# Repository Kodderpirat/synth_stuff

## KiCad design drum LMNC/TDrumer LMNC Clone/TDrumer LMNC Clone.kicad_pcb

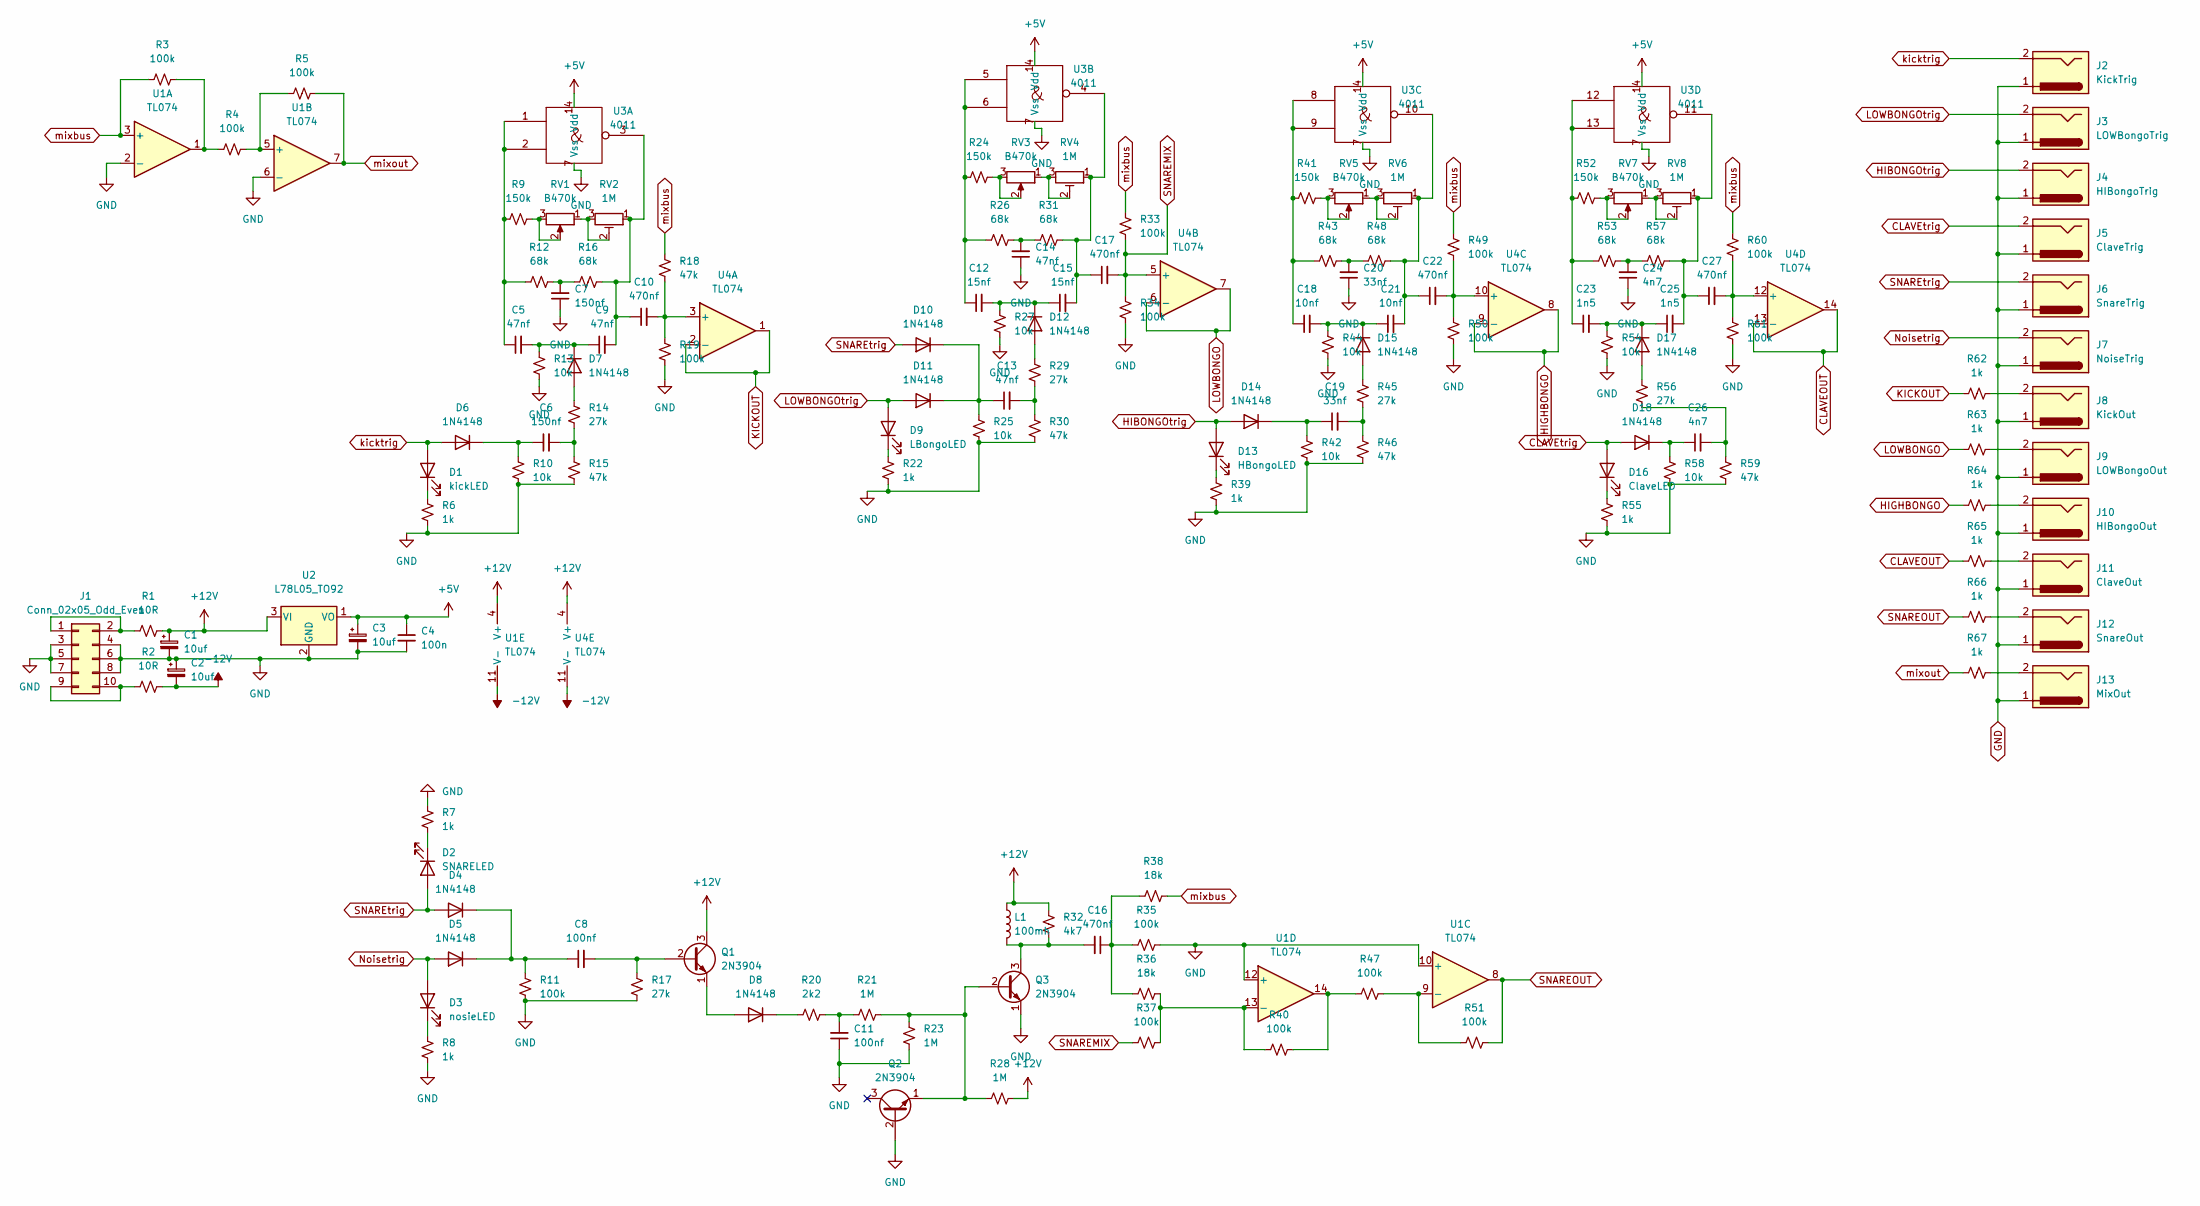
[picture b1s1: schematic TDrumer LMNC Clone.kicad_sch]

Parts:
C1, C2, C3: 10uf; CP_Radial_D5.0mm_P2.50mm
C4: 100n; C_Disc_D6.0mm_W2.5mm_P5.00mm
C5, C9, C13, C14: 47nf; C_Disc_D6.0mm_W2.5mm_P5.00mm
C6, C7: 150nf; C_Disc_D6.0mm_W2.5mm_P5.00mm
C8, C11: 100nf; C_Disc_D6.0mm_W2.5mm_P5.00mm
C10, C16, C17, C22, C27: 470nf; C_Disc_D6.0mm_W2.5mm_P5.00mm
C12, C15: 15nf; C_Disc_D6.0mm_W2.5mm_P5.00mm
C18, C21: 10nf; C_Disc_D6.0mm_W2.5mm_P5.00mm
C19, C20: 33nf; C_Disc_D6.0mm_W2.5mm_P5.00mm
C23, C25: 1n5; C_Disc_D6.0mm_W2.5mm_P5.00mm
C24, C26: 4n7; C_Disc_D6.0mm_W2.5mm_P5.00mm
D1: kickLED; PinSocket_1x02_P2.54mm_Vertical
D2: SNARELED; PinSocket_1x02_P2.54mm_Vertical
D3: nosieLED; PinSocket_1x02_P2.54mm_Vertical
D4, D5, D6, D7, D8, D10, D11, D12, D14, D15, D17, D18: 1N4148; D_DO-35_SOD27_P7.62mm_Horizontal
D9: LBongoLED; PinSocket_1x02_P2.54mm_Vertical
D13: HBongoLED; PinSocket_1x02_P2.54mm_Vertical
D16: ClaveLED; PinSocket_1x02_P2.54mm_Vertical
J1: Conn_02x05_Odd_Even; PinSocket_2x05_P2.54mm_Vertical
J2: KickTrig; PinSocket_1x02_P2.54mm_Vertical
J3: LOWBongoTrig; PinSocket_1x02_P2.54mm_Vertical
J4: HIBongoTrig; PinSocket_1x02_P2.54mm_Vertical
J5: ClaveTrig; PinSocket_1x02_P2.54mm_Vertical
J6: SnareTrig; PinSocket_1x02_P2.54mm_Vertical
J7: NoiseTrig; PinSocket_1x02_P2.54mm_Vertical
J8: KickOut; PinSocket_1x02_P2.54mm_Vertical
J9: LOWBongoOut; PinSocket_1x02_P2.54mm_Vertical
J10: HIBongoOut; PinSocket_1x02_P2.54mm_Vertical
J11: ClaveOut; PinSocket_1x02_P2.54mm_Vertical
J12: SnareOut; PinSocket_1x02_P2.54mm_Vertical
J13: MixOut; PinSocket_1x02_P2.54mm_Vertical
L1: 100mh; L_Axial_L17.5mm_D12.0mm_P20.32mm_Horizontal_Vishay_IM-10-46
Q1, Q2, Q3: 2N3904; TO-92_Inline
R1, R2: 10R; R_Axial_DIN0204_L3.6mm_D1.6mm_P7.62mm_Horizontal
R3, R4, R5, R11, R19, R33, R34, R35, R37, R40, R47, R49, R50, R51, R60, R61: 100k; R_Axial_DIN0204_L3.6mm_D1.6mm_P7.62mm_Horizontal
R6, R7, R8, R22, R39, R55, R62, R63, R64, R65, R66, R67: 1k; R_Axial_DIN0204_L3.6mm_D1.6mm_P7.62mm_Horizontal
R9, R24, R41, R52: 150k; R_Axial_DIN0204_L3.6mm_D1.6mm_P7.62mm_Horizontal
R10, R13, R25, R27, R42, R44, R54, R58: 10k; R_Axial_DIN0204_L3.6mm_D1.6mm_P7.62mm_Horizontal
R12, R16, R26, R31, R43, R48, R53, R57: 68k; R_Axial_DIN0204_L3.6mm_D1.6mm_P7.62mm_Horizontal
R14, R17, R29, R45, R56: 27k; R_Axial_DIN0204_L3.6mm_D1.6mm_P7.62mm_Horizontal
R15, R18, R30, R46, R59: 47k; R_Axial_DIN0204_L3.6mm_D1.6mm_P7.62mm_Horizontal
R20: 2k2; R_Axial_DIN0204_L3.6mm_D1.6mm_P7.62mm_Horizontal
R21, R23, R28: 1M; R_Axial_DIN0204_L3.6mm_D1.6mm_P7.62mm_Horizontal
R32: 4k7; R_Axial_DIN0204_L3.6mm_D1.6mm_P7.62mm_Horizontal
R36, R38: 18k; R_Axial_DIN0204_L3.6mm_D1.6mm_P7.62mm_Horizontal
RV1, RV3, RV5, RV7: B470k; PinSocket_1x03_P2.54mm_Vertical
RV2, RV4, RV6, RV8: 1M; PinSocket_1x03_P2.54mm_Vertical
U1, U4: TL074; DIP-14_W7.62mm
U2: L78L05_TO92; TO-92_Inline
U3: 4011; DIP-14_W7.62mm

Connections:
+5V: C3.1, C4.1, U2.1 (VO), U3.14 (Vdd)
+12V: C1.1, L1.1, Q1.3 (C), R1.2, R28.1, R32.2, U1.4 (V+), U2.3 (VI), U4.4 (V+)
-12V: C2.2, R2.2, U1.11 (V-), U4.11 (V-)
CLAVEOUT: R65.1, U4.13 (-), U4.14
CLAVEtrig: D16.2 (A), D18.2 (A), J5.2
GND: C1.2, C2.1, C3.2, C4.2, C7.1, C11.1, C14.1, C20.1, C24.1, J1.3, J1.4, J1.5, J1.6, J1.7, J1.8, J2.1, J3.1, J4.1, J5.1, J6.1, J7.1, J8.1, J9.1, J10.1, J11.1, J12.1, J13.1, Q2.2 (B), Q3.1 (E), R6.2, R7.1, R8.2, R10.2, R11.2, R13.2, R15.2, R17.2, R19.2, R22.2, R23.1, R25.2, R27.2, R30.2, R34.2, R35.2, R39.2, R42.2, R44.2, R46.2, R50.2, R54.2, R55.2, R58.2, R59.2, R61.2, U1.2 (-), U1.6 (-), U1.10 (+), U1.12 (+), U2.2 (GND), U3.7 (Vss)
HIBONGOtrig: D13.2 (A), D14.2 (A), J4.2
HIGHBONGO: R64.1, U4.8, U4.9 (-)
KICKOUT: R62.1, U4.1, U4.2 (-)
LOWBONGO: R63.1, U4.6 (-), U4.7
LOWBONGOtrig: D9.2 (A), D11.2 (A), J3.2
unnamed: C5.1, R9.1, R12.1, U3.1, U3.2
unnamed: C5.2, C9.1, D7.1 (K), R13.1
unnamed: C6.1, D6.1 (K), R10.1
unnamed: C6.2, R14.2, R15.1
unnamed: C7.2, R12.2, R16.1
unnamed: C8.1, D4.1 (K), D5.1 (K), R11.1
unnamed: C8.2, Q1.2 (B), R17.1
unnamed: C9.2, C10.1, R16.2, RV2.1, U3.3
unnamed: C10.2, R18.2, R19.1, U4.3 (+)
unnamed: C11.2, R20.2, R21.1
unnamed: C12.1, R24.1, R26.1, U3.5, U3.6
unnamed: C12.2, C15.1, D12.1 (K), R27.1
unnamed: C13.1, D10.1 (K), D11.1 (K), R25.1
unnamed: C13.2, R29.2, R30.1
unnamed: C14.2, R26.2, R31.1
unnamed: C15.2, C17.1, R31.2, RV4.1, U3.4
unnamed: C16.1, R35.1, R36.1, R38.1
unnamed: C16.2, L1.2, Q3.3 (C), R32.1
unnamed: C18.1, R41.1, R43.1, U3.8, U3.9
unnamed: C18.2, C21.1, D15.1 (K), R44.1
unnamed: C19.1, D14.1 (K), R42.1
unnamed: C19.2, R45.2, R46.1
unnamed: C20.2, R43.2, R48.1
unnamed: C21.2, C22.1, R48.2, RV6.1, U3.10
unnamed: C22.2, R49.2, R50.1, U4.10 (+)
unnamed: C23.1, R52.1, R53.1, U3.12, U3.13
unnamed: C23.2, C25.1, D17.1 (K), R54.1
unnamed: C24.2, R53.2, R57.1
unnamed: C25.2, C27.1, R57.2, RV8.1, U3.11
unnamed: C26.1, D18.1 (K), R58.1
unnamed: C26.2, R56.2, R59.1
unnamed: C27.2, R60.2, R61.1, U4.12 (+)
unnamed: D1.1 (K), R6.1
unnamed: D2.1 (K), R7.2
unnamed: D3.1 (K), R8.1
unnamed: D7.2 (A), R14.1
unnamed: D8.1 (K), R20.1
unnamed: D8.2 (A), Q1.1 (E)
unnamed: D9.1 (K), R22.1
unnamed: D12.2 (A), R29.1
unnamed: D13.1 (K), R39.1
unnamed: D15.2 (A), R45.1
unnamed: D16.1 (K), R55.1
unnamed: D17.2 (A), R56.1
unnamed: J1.1, J1.2, R1.1
unnamed: J1.9, J1.10, R2.1
unnamed: J8.2, R62.2
unnamed: J9.2, R63.2
unnamed: J10.2, R64.2
unnamed: J11.2, R65.2
unnamed: J12.2, R66.2
unnamed: J13.2, R67.2
unnamed: Q2.1 (E), Q3.2 (B), R21.2, R23.2, R28.2
unnamed: R3.2, R4.1, U1.1
unnamed: R4.2, R5.1, U1.5 (+)
unnamed: R9.2, RV1.2, RV1.3
unnamed: R24.2, RV3.2, RV3.3
unnamed: R36.2, R37.2, R40.1, U1.13 (-)
unnamed: R40.2, R47.1, U1.14
unnamed: R41.2, RV5.2, RV5.3
unnamed: R47.2, R51.1, U1.9 (-)
unnamed: R52.2, RV7.2, RV7.3
unnamed: RV1.1, RV2.2, RV2.3
unnamed: RV3.1, RV4.2, RV4.3
unnamed: RV5.1, RV6.2, RV6.3
unnamed: RV7.1, RV8.2, RV8.3
Noisetrig: D3.2 (A), D5.2 (A), J7.2
SNAREMIX: C17.2, R33.2, R34.1, R37.1, U4.5 (+)
SNAREOUT: R51.2, R66.1, U1.8
SNAREtrig: D2.2 (A), D4.2 (A), D10.2 (A), J6.2
kicktrig: D1.2 (A), D6.2 (A), J2.2
mixbus: R3.1, R18.1, R33.1, R38.2, R49.1, R60.1, U1.3 (+)
mixout: R5.2, R67.1, U1.7

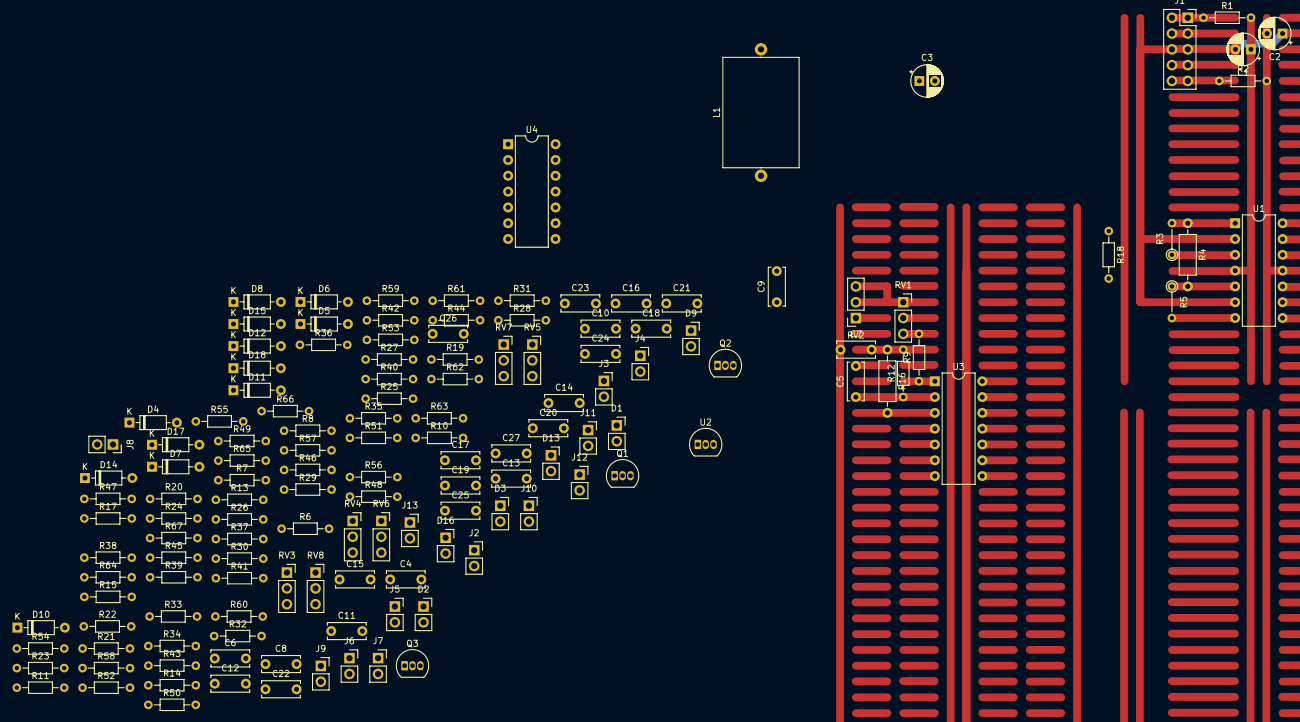
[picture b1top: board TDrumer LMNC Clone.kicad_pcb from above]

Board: 2 copper layers, 141 parts (0 on the bottom side), 84 nets.

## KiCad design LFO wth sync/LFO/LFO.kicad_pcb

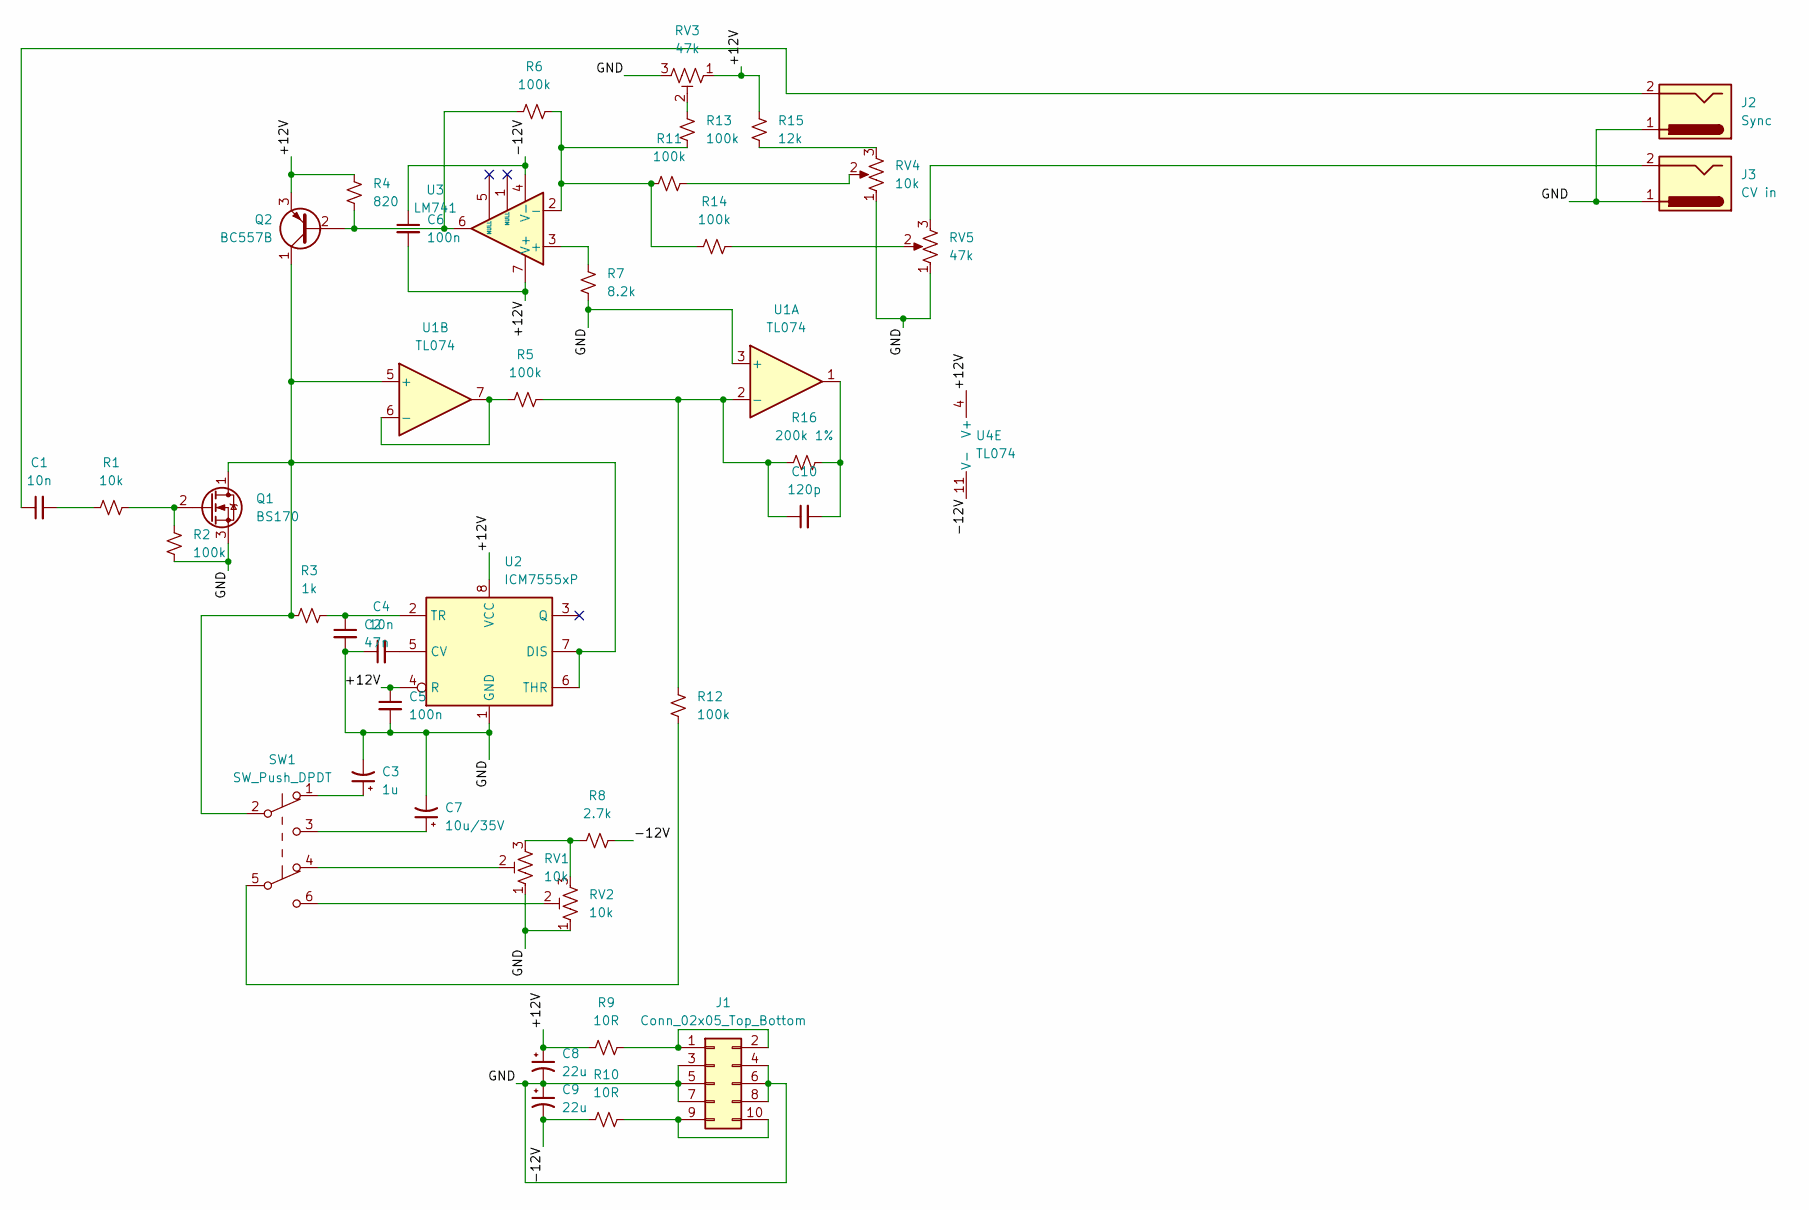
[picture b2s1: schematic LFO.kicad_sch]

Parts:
C1, C4: 10n; C_Disc_D10.5mm_W5.0mm_P5.00mm
C2: 47n; C_Disc_D10.5mm_W5.0mm_P5.00mm
C3: 1u; CP_Radial_D6.3mm_P2.50mm
C5, C6: 100n; C_Disc_D10.5mm_W5.0mm_P5.00mm
C7: 10u/35V; CP_Radial_D6.3mm_P2.50mm
C8, C9: 22u; CP_Radial_D6.3mm_P2.50mm
C10: 120p; C_Disc_D10.5mm_W5.0mm_P5.00mm
J1: Conn_02x05_Top_Bottom; PinHeader_2x05_P2.54mm_Vertical
J2: Sync; PinHeader_1x02_P2.54mm_Vertical
J3: CV in; PinHeader_1x02_P2.54mm_Vertical
Q1: BS170; TO-92_Inline
Q2: BC557B; TO-92_Inline
R1: 10k; R_Axial_DIN0207_L6.3mm_D2.5mm_P7.62mm_Horizontal
R2, R5, R6, R11, R12, R13, R14: 100k; R_Axial_DIN0207_L6.3mm_D2.5mm_P7.62mm_Horizontal
R3: 1k; R_Axial_DIN0207_L6.3mm_D2.5mm_P7.62mm_Horizontal
R4: 820; R_Axial_DIN0207_L6.3mm_D2.5mm_P7.62mm_Horizontal
R7: 8.2k; R_Axial_DIN0207_L6.3mm_D2.5mm_P7.62mm_Horizontal
R8: 2.7k; R_Axial_DIN0207_L6.3mm_D2.5mm_P7.62mm_Horizontal
R9, R10: 10R; R_Axial_DIN0207_L6.3mm_D2.5mm_P7.62mm_Horizontal
R15: 12k; R_Axial_DIN0207_L6.3mm_D2.5mm_P7.62mm_Horizontal
R16: 200k 1%; R_Axial_DIN0207_L6.3mm_D2.5mm_P7.62mm_Horizontal
RV1, RV2: 10k; Potentiometer_Bourns_3386C_Horizontal
RV3: 47k; Potentiometer_Bourns_3386C_Horizontal
RV4: 10k; PinHeader_1x03_P2.54mm_Vertical
RV5: 47k; PinHeader_1x03_P2.54mm_Vertical
SW1: SW_Push_DPDT; PinHeader_1x06_P2.54mm_Vertical
U1: TL074; DIP-14_W7.62mm
U2: ICM7555xP; DIP-8_W7.62mm
U3: LM741; DIP-8_W7.62mm
U4: TL074

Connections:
/+12V: C5.1, C6.2, C8.1, Q2.3 (E), R4.1, R9.1, R15.1, RV3.1, U1.4 (V+), U2.4 (R), U2.8 (VCC), U3.7 (V+), U4.4 (V+)
/-12V: C6.1, C9.2, R8.2, R10.1, U1.11 (V-), U3.4 (V-), U4.11 (V-)
/GND: C2.2, C3.2, C4.1, C5.2, C7.2, C8.2, C9.1, J1.3, J1.4, J1.5, J1.6, J1.7, J1.8, J2.1, J3.1, Q1.3 (S), R2.1, R7.2, RV1.1, RV2.1, RV3.3, RV4.1, RV5.1, U1.3 (+), U2.1 (GND)
unnamed: C1.1, J2.2
unnamed: C1.2, R1.1
unnamed: C2.1, R3.2, U2.2 (TR)
unnamed: C3.1, SW1.1 (A)
unnamed: C4.2, U2.5 (CV)
unnamed: C10.1, R5.2, R12.1, R16.1, U1.2 (-)
unnamed: C10.2, R16.2, U1.1
unnamed: J3.2, RV5.3
unnamed: Q1.1 (D), Q2.1 (C), R3.1, SW1.2 (B), U1.5 (+), U2.6 (THR), U2.7 (DIS)
unnamed: Q1.2 (G), R1.2, R2.2
unnamed: Q2.2 (B), R4.2, R6.1, U3.6
unnamed: R5.1, U1.6 (-), U1.7
unnamed: R7.1, U3.3 (+)
unnamed: R8.1, RV1.3, RV2.3
unnamed: J1.1, J1.2, R9.2
unnamed: J1.9, J1.10, R10.2
unnamed: R6.2, R11.1, R13.2, R14.1, U3.2 (-)
unnamed: R11.2, RV4.2
unnamed: R12.2, SW1.5 (B)
unnamed: R13.1, RV3.2
unnamed: R14.2, RV5.2
unnamed: R15.2, RV4.3
unnamed: RV1.2, SW1.4 (A)
unnamed: RV2.2, SW1.6 (C)
unnamed: C7.1, SW1.3 (C)

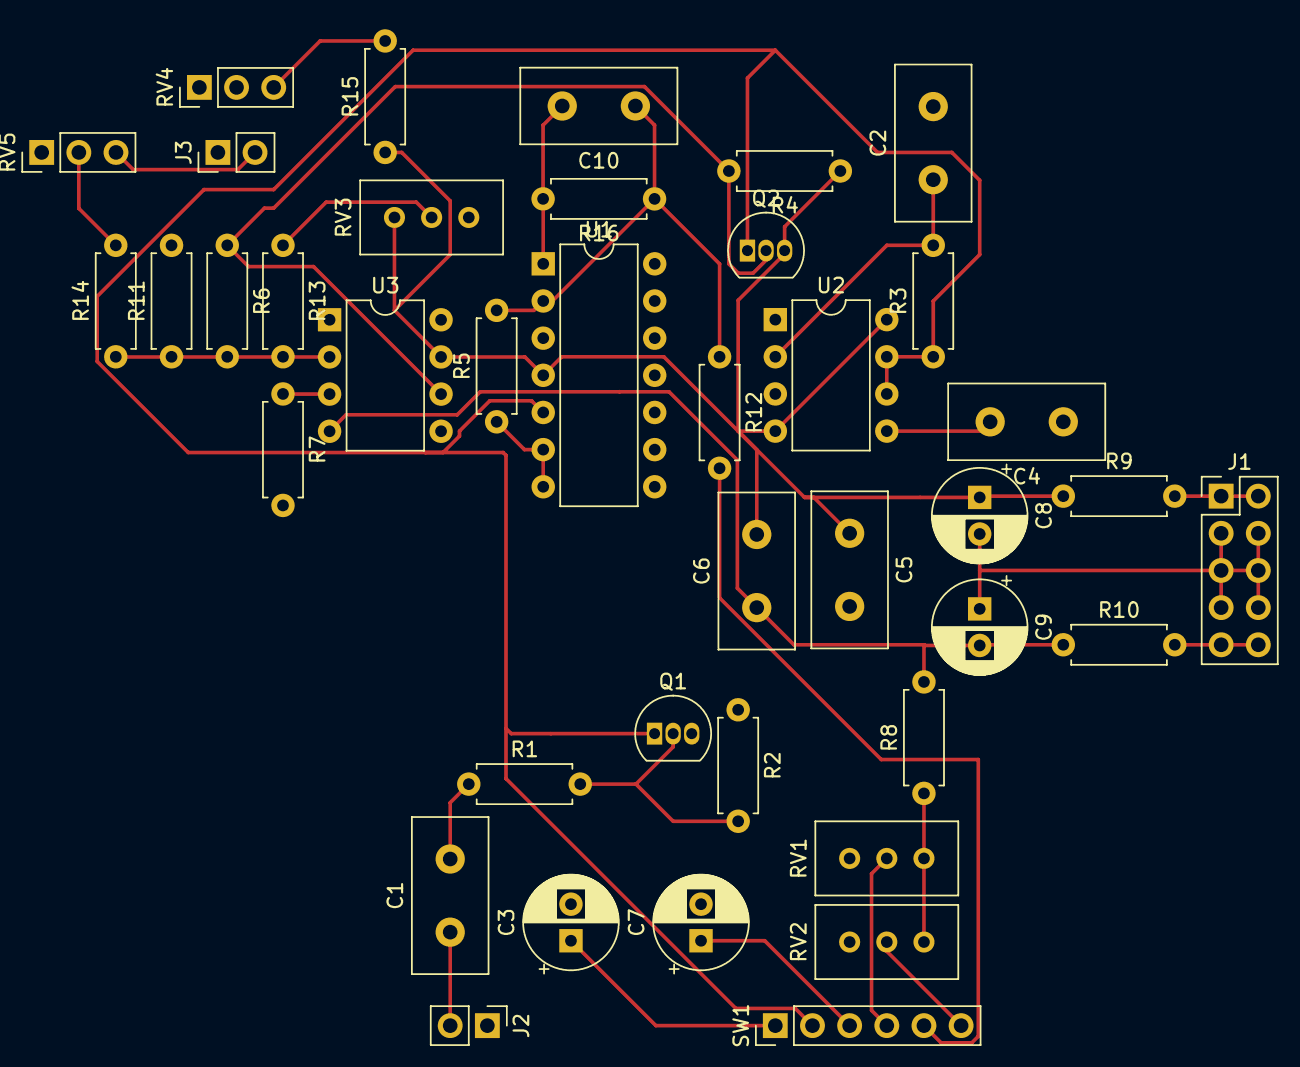
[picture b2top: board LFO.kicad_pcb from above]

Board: 2 copper layers, 40 parts (0 on the bottom side), 28 nets.

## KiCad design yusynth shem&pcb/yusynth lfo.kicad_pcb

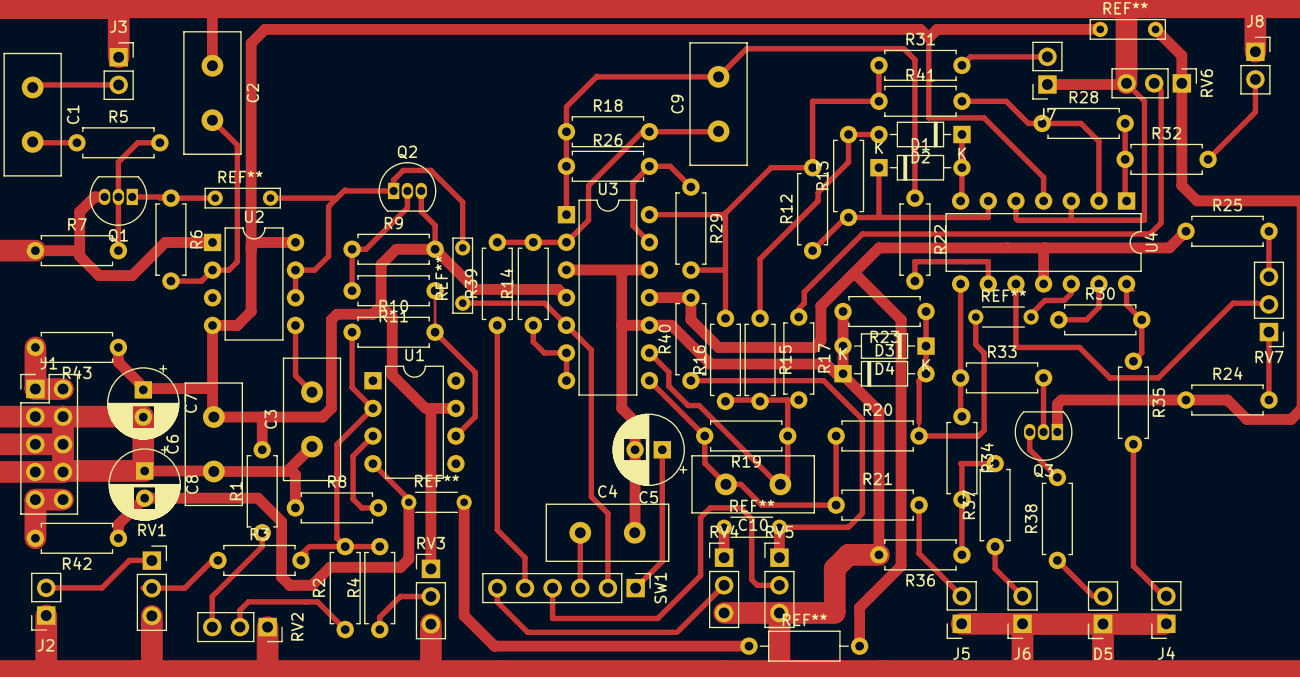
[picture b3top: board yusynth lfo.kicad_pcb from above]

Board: 2 copper layers, 80 parts (0 on the bottom side), 56 nets.

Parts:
C1, C3: 10nf; C_Disc_D11.0mm_W5.0mm_P5.00mm
C2: 47nf; C_Disc_D11.0mm_W5.0mm_P5.00mm
C4: 1uf; C_Disc_D11.0mm_W5.0mm_P5.00mm
C5: 10uf/35V; CP_Radial_D6.3mm_P2.50mm
C6: 100nf; C_Disc_D11.0mm_W5.0mm_P5.00mm
C7: 10 uf; CP_Radial_D6.3mm_P2.50mm
C8: 10uf; CP_Radial_D6.3mm_P2.50mm
C9: 120pf; C_Disc_D11.0mm_W5.0mm_P5.00mm
C10: 1nf; C_Disc_D11.0mm_W5.0mm_P5.00mm
D1, D2, D3, D4: 1N4148; D_DO-35_SOD27_P7.62mm_Horizontal
D5: LED; PinSocket_1x02_P2.54mm_Vertical
J1: Conn_02x05_Top_Bottom; PinHeader_2x05_P2.54mm_Vertical
J2: CV; PinSocket_1x02_P2.54mm_Vertical
J3: SYNC; PinSocket_1x02_P2.54mm_Vertical
J4: SINE; PinSocket_1x02_P2.54mm_Vertical
J5: TRI; PinSocket_1x02_P2.54mm_Vertical
J6: PULSE; PinSocket_1x02_P2.54mm_Vertical
J7: SAW; PinSocket_1x02_P2.54mm_Vertical
J8: RAMP; PinSocket_1x02_P2.54mm_Vertical
Q1: BS170; TO-92_Inline
Q2: BC557; TO-92_Inline
Q3: BC547; TO-92_Inline
R1, R36: 12k; R_Axial_DIN0207_L6.3mm_D2.5mm_P7.62mm_Horizontal
R2, R3, R4, R7, R10, R12, R13, R14, R16, R26, R28, R39, R41: 100k; R_Axial_DIN0207_L6.3mm_D2.5mm_P7.62mm_Horizontal
R5, R22, R34: 10k; R_Axial_DIN0207_L6.3mm_D2.5mm_P7.62mm_Horizontal
R6, R21, R31, R32, R35, R37, R38: 1k; R_Axial_DIN0207_L6.3mm_D2.5mm_P7.62mm_Horizontal
R8: 8.2k; R_Axial_DIN0207_L6.3mm_D2.5mm_P7.62mm_Horizontal
R9: 820R; R_Axial_DIN0207_L6.3mm_D2.5mm_P7.62mm_Horizontal
R11: 27k; R_Axial_DIN0207_L6.3mm_D2.5mm_P7.62mm_Horizontal
R15: 50k; R_Axial_DIN0207_L6.3mm_D2.5mm_P7.62mm_Horizontal
R17, R20: 150k; R_Axial_DIN0207_L6.3mm_D2.5mm_P7.62mm_Horizontal
R18, R19, R29: 200k; R_Axial_DIN0207_L6.3mm_D2.5mm_P7.62mm_Horizontal
R23: 22k; R_Axial_DIN0207_L6.3mm_D2.5mm_P7.62mm_Horizontal
R24, R25, R30: 15k; R_Axial_DIN0207_L6.3mm_D2.5mm_P7.62mm_Horizontal
R33: 47k; R_Axial_DIN0207_L6.3mm_D2.5mm_P7.62mm_Horizontal
R40: 2.7k; R_Axial_DIN0207_L6.3mm_D2.5mm_P7.62mm_Horizontal
R42, R43: 100R; R_Axial_DIN0207_L6.3mm_D2.5mm_P7.62mm_Horizontal
RV1: 50k; PinSocket_1x03_P2.54mm_Vertical
RV2: 10k; PinSocket_1x03_P2.54mm_Vertical
RV3, RV6: 50k; PinHeader_1x03_P2.54mm_Vertical
RV4, RV5, RV7: 10k; PinHeader_1x03_P2.54mm_Vertical
SW1: SW_Push_DPDT; PinHeader_1x06_P2.54mm_Vertical
U1: LM741; DIP-8_W7.62mm
U2: NE555P; DIP-8_W7.62mm
U3, U4: TL074; DIP-14_W7.62mm

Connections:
+12V: C6.2, C7.1, Q2.3 (E), Q3.1 (C), R1.2, R9.2, R24.1, R43.1, RV3.1, RV6.1, U1.7 (V+), U2.4 (R), U2.8 (VCC), U3.4 (V+), U4.4 (V+)
-12V: C8.2, R25.1, R40.2, R42.1, U1.4 (V-), U3.11 (V-), U4.11 (V-)
GND: C2.1, C3.1, C4.2, C5.2, C6.1, C7.2, C8.1, D3.1 (K), D4.2 (A), D5.1 (K), J1.3, J1.4, J1.5, J1.6, J1.7, J1.8, J2.1, J3.1, J4.1, J5.1, J6.1, J7.1, J8.1, Q1.3 (S), R7.1, R8.1, R23.2, R36.2, RV1.3, RV2.1, RV3.3, RV4.3, RV5.3, RV6.3, U2.1 (GND), U3.3 (+), U3.10 (+), U3.12 (+), U4.3 (+), U4.5 (+)
unnamed: C1.2, R5.1
unnamed: C2.2, R6.2, U2.2 (TR)
unnamed: C3.2, U2.5 (CV)
unnamed: C4.1, SW1.3 (C)
unnamed: C5.1, SW1.1 (A)
unnamed: C9.1, R14.2, R18.2, R39.2, U3.2 (-)
unnamed: C9.2, R18.1, R22.1, R26.1, U3.1
unnamed: C10.1, R15.2, R16.1, R17.2, R19.1, U3.9 (-)
unnamed: C10.2, R19.2, R20.1, R21.1, U3.8
unnamed: D1.1 (K), R12.1, R13.1, U4.6 (-)
unnamed: D1.2 (A), D2.1 (K), U4.7
unnamed: D2.2 (A), R13.2, R15.1
unnamed: D3.2 (A), D4.1 (K), R20.2, R23.1, U4.12 (+)
unnamed: D5.2 (A), R38.1
unnamed: J1.1, J1.2, R43.2
unnamed: J1.9, J1.10, R42.2
unnamed: J2.2, RV1.1
unnamed: J4.2, R35.2
unnamed: Q1.1 (D), Q2.1 (C), R6.1, SW1.2 (B), U2.6 (THR), U2.7 (DIS), U3.5 (+)
unnamed: Q1.2 (G), R5.2, R7.2
unnamed: Q2.2 (B), R9.1, R11.2
unnamed: Q3.2 (B), R33.2
unnamed: Q3.3 (E), R38.2
unnamed: R1.1, RV2.3
unnamed: R2.1, RV2.2
unnamed: R3.1, RV1.2
unnamed: R4.1, RV3.2
unnamed: R8.2, U1.3 (+)
unnamed: R2.2, R3.2, R4.2, R10.1, U1.2 (-)
unnamed: R10.2, R11.1, U1.6
unnamed: R12.2, R16.2, R29.2, R31.1, R41.1, U3.14
unnamed: R14.1, U3.6 (-), U3.7
unnamed: R17.1, RV6.2
unnamed: R22.2, U4.9 (-)
unnamed: R24.2, RV7.1
unnamed: R25.2, RV7.3
unnamed: R26.2, R29.1, U3.13 (-)
unnamed: R30.1, U4.13 (-)
unnamed: R28.1, R41.2, U4.2 (-)
unnamed: R28.2, R32.1, U4.1
unnamed: R30.2, R35.1, U4.14
unnamed: R33.1, R34.1, U4.8
unnamed: R34.2, R36.1, R37.2
unnamed: R39.1, SW1.5 (B)
unnamed: R40.1, RV4.1, RV5.1
unnamed: RV4.2, SW1.6 (C)
unnamed: RV5.2, SW1.4 (A)
unnamed: RV7.2, U4.10 (+)
PULSE: J6.2, R37.1
RAMP: J8.2, R32.2
SAW: J7.2, R31.2
SYNC: C1.1, J3.2
TRI: J5.2, R21.2

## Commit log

2023-01-12 add project
2023-07-09 updated APC shematic
2023-07-09 adds APC shematic pdf
